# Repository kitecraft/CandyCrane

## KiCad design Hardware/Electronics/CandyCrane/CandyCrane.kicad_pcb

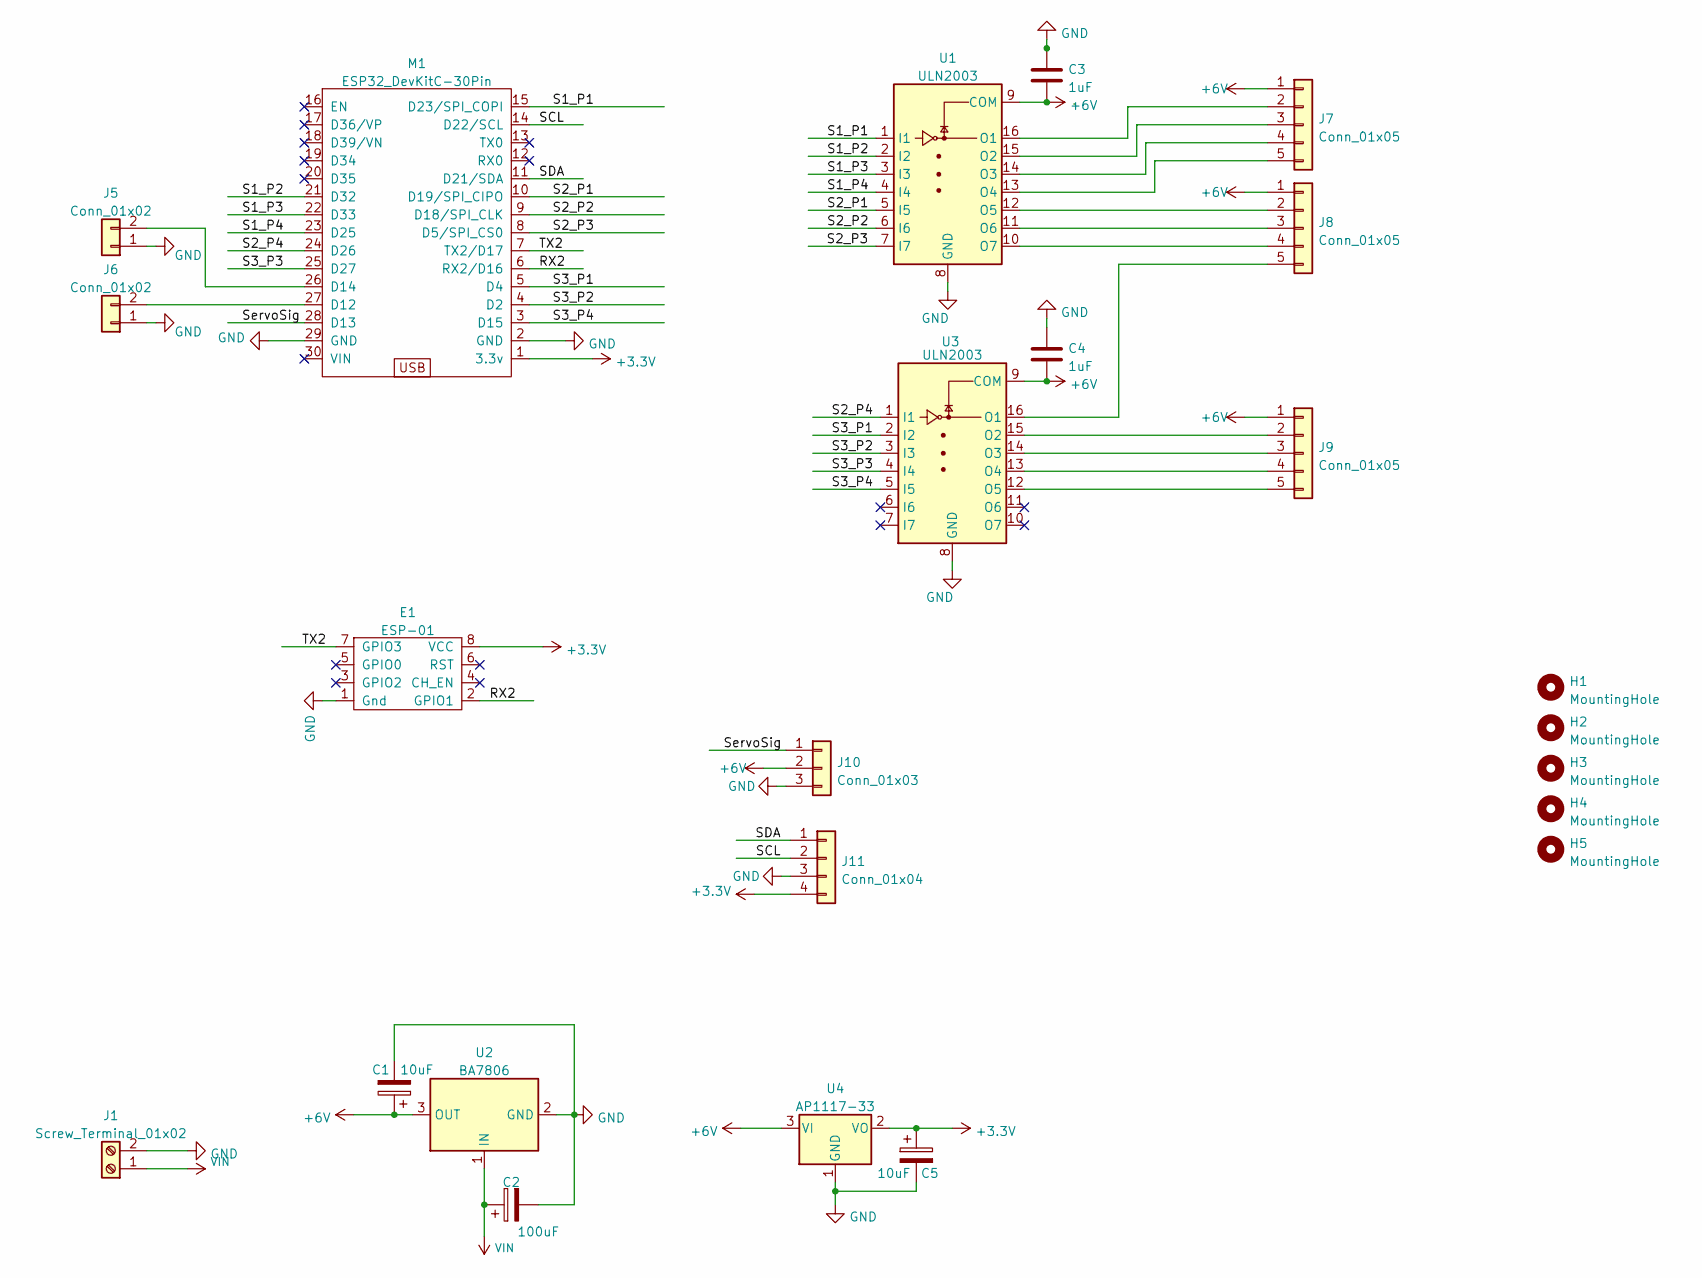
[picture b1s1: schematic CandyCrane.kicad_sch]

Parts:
C1, C5: 10uF; CP_EIA-3216-12_Kemet-S_Pad1.58x1.35mm_HandSolder
C2: 100uF; CP_Elec_6.3x5.9
C3, C4: 1uF; C_0805_2012Metric
E1: ESP-01; ESP-01_With_Header
H1, H2, H3, H4, H5: MountingHole; MountingHole_2.7mm
J1: Screw_Terminal_01x02; TerminalBlock_Phoenix_MKDS-1,5-2-5.08_1x02_P5.08mm_Horizont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
J5, J6: Conn_01x02; PinHeader_1x02_P2.54mm_Vertical
J7, J8, J9: Conn_01x05; PinHeader_1x05_P2.54mm_Vertical
J10: Conn_01x03; PinHeader_1x03_P2.54mm_Vertical
J11: Conn_01x04; PinHeader_1x04_P2.54mm_Vertical
M1: ESP32_DevKitC-30Pin; ESP32S_30Pin
U1, U3: ULN2003; ULN2003 on Socket
U2: BA7806; TO-252-2
U4: AP1117-33; SOT-223-3_TabPin2

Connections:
+3V3: C5.1, E1.8 (VCC), J11.4, M1.1 (3.3v), U4.2 (VO)
+6V: C1.1, C3.2, C4.2, J7.1, J8.1, J9.1, J10.2, U1.9 (COM), U2.3 (OUT), U3.9 (COM), U4.3 (VI)
/RX2: E1.2 (GPIO1), M1.6 (RX2/D16)
/S1_P1: M1.15 (D23/SPI_COPI), U1.1 (I1)
/S1_P2: M1.21 (D32), U1.2 (I2)
/S1_P3: M1.22 (D33), U1.3 (I3)
/S1_P4: M1.23 (D25), U1.4 (I4)
/S2_P1: M1.10 (D19/SPI_CIPO), U1.5 (I5)
/S2_P2: M1.9 (D18/SPI_CLK), U1.6 (I6)
/S2_P3: M1.8 (D5/SPI_CS0), U1.7 (I7)
/S2_P4: M1.24 (D26), U3.1 (I1)
/S3_P1: M1.5 (D4), U3.2 (I2)
/S3_P2: M1.4 (D2), U3.3 (I3)
/S3_P3: M1.25 (D27), U3.4 (I4)
/S3_P4: M1.3 (D15), U3.5 (I5)
/SCL: J11.2, M1.14 (D22/SCL)
/SDA: J11.1, M1.11 (D21/SDA)
/ServoSig: J10.1, M1.28 (D13)
/TX2: E1.7 (GPIO3), M1.7 (TX2/D17)
GND: C1.2, C2.2, C3.1, C4.1, C5.2, E1.1 (Gnd), J1.2, J5.1, J6.1, J10.3, J11.3, M1.2 (GND), M1.29 (GND), U1.8 (GND), U2.2 (GND), U3.8 (GND), U4.1 (GND)
unnamed: J5.2, M1.26 (D14)
unnamed: J6.2, M1.27 (D12)
unnamed: J7.2, U1.16 (O1)
unnamed: J7.3, U1.15 (O2)
unnamed: J7.4, U1.14 (O3)
unnamed: J7.5, U1.13 (O4)
unnamed: J8.2, U1.12 (O5)
unnamed: J8.3, U1.11 (O6)
unnamed: J8.4, U1.10 (O7)
unnamed: J8.5, U3.16 (O1)
unnamed: J9.2, U3.15 (O2)
unnamed: J9.3, U3.14 (O3)
unnamed: J9.4, U3.13 (O4)
unnamed: J9.5, U3.12 (O5)
VIN: C2.1, J1.1, U2.1 (IN)

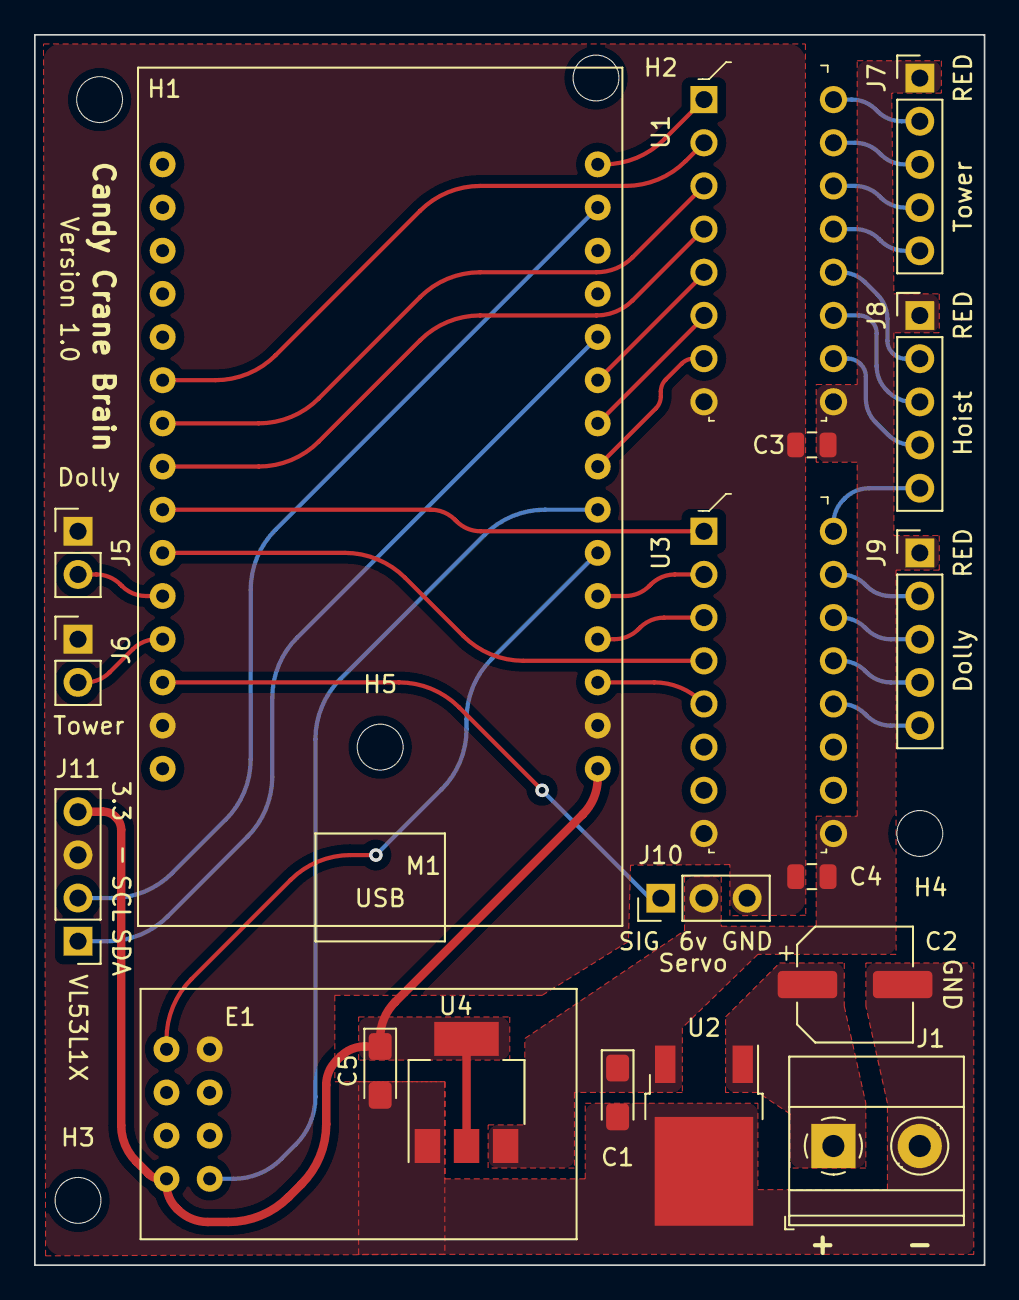
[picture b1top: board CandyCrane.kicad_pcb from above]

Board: 2 copper layers, 55.9 x 72.4 mm, 24 parts (0 on the bottom side), 35 nets.

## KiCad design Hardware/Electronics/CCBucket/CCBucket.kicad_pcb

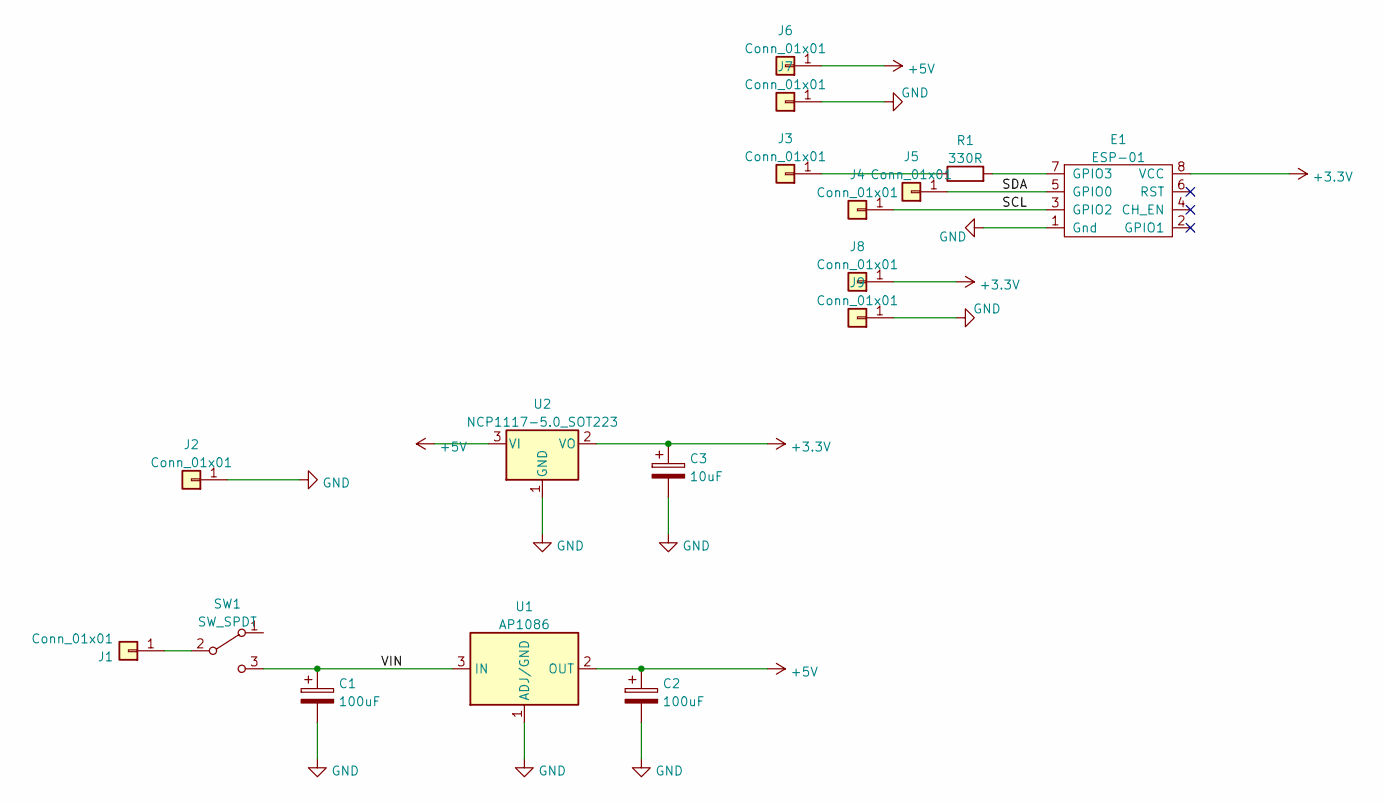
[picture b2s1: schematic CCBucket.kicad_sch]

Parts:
C1, C2: 100uF; CP_Elec_6.3x5.9
C3: 10uF; C_0805_2012Metric
E1: ESP-01; ESP-01_With_Header
J1, J2, J3, J4, J5, J6, J7, J8, J9: Conn_01x01; 1X01
R1: 330R; R_0201_0603Metric
SW1: SW_SPDT; SPDT_Switch_3mm
U1: AP1086; TO-263-2
U2: NCP1117-5.0_SOT223; SOT-223-3_TabPin2

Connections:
+3V3: C3.1, E1.8 (VCC), J8.1, U2.2 (VO)
+5V: C2.1, J6.1, U1.2 (OUT), U2.3 (VI)
/SCL: E1.3 (GPIO2), J4.1
/SDA: E1.5 (GPIO0), J5.1
/VIN: C1.1, SW1.3 (C), U1.3 (IN)
GND: C1.2, C2.2, C3.2, E1.1 (Gnd), J2.1, J7.1, J9.1, U1.1 (ADJ/GND), U2.1 (GND)
unnamed: E1.7 (GPIO3), R1.2
unnamed: J1.1, SW1.2 (B)
unnamed: J3.1, R1.1

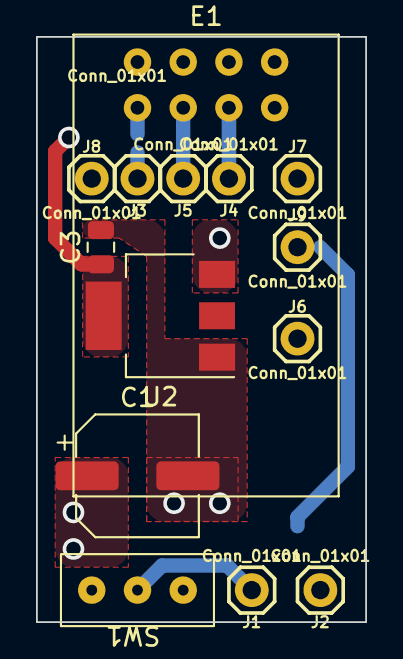
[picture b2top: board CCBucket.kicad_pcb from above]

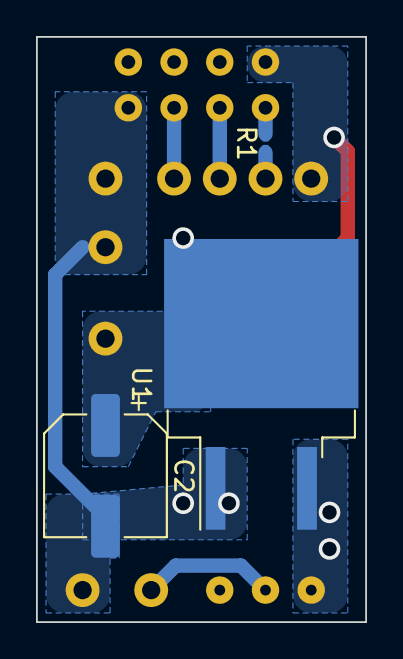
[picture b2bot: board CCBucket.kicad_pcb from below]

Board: 2 copper layers, 18.3 x 32.5 mm, 17 parts (3 on the bottom side), 9 nets.

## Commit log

2022-03-27 And again.
2022-03-29 Updtes
2022-03-29 Working with geting bucket distance, as well as open and close the bucket.
2022-04-12 Many Updates
2022-04-12 Added Rope Barrel
2022-04-21 Added CCBucket PCB
2022-04-24 Added circuit board for bucket controller
2022-04-28 Updated step file and some source for new DevKitC
2022-05-06 Added the new CCComms module.
2022-05-06 Working OTA, Webserver
2022-05-07 Mostly working now.
2022-05-08 Bucket Calibration
2022-05-08 Small updates
2022-05-08 Essentially working crane with automation
2022-05-11 Nearly there.
2022-05-12 Added SmallFlexyStepper and began the move to useing it.
2022-05-12 Moved Tower and Dolly over to the new SmallFlexyStepper Still need to tweek the dolly a bit more.
2022-05-13 Minor updates
2022-05-16 More updates
2022-05-21 Updated step file (CAD design)
2022-05-21 Adding more files for the Candy Crane Brain
2022-05-25 Much work on the final stepper drivers. Adding the Kicad project for Candy Cane Brain
2022-05-26 Use ServoEasing as a pointer in CandyRanger seems to work (at least no compile errors now).
2022-05-26 Useing ServoEasing as a pointer seems to fix the comple problems. ServoEasing *_servo = nullptr;
2023-01-22 Converted over to TCP server for Crane<->Bucket communication. Switching to use MultiTinyStepper for stepper control.
2023-01-27 Much progress
2023-09-08 Switching over to my SmallFlexyStepper class
